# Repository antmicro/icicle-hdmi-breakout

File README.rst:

====================
Icicle HDMI breakout
====================

Copyright (c) 2020 `Antmicro <https://www.antmicro.com>`_

.. figure:: img/icicle-hdmi-breakout.png

Overview
========

This repository contains open hardware design files for Antmicro's expansion board compatible with the `PolarFire SoC FPGA Icicle Evaluation Kit from Microchip. <https://www.microsemi.com/existing-parts/parts/152514>`_.
The design files were created in KiCad.
The expansion board breaks out an HDMI interface on a regular HDMI connector.
The TMDS data going out of this connector are connected to the FPGA fabric in `MPFS250T-FCVG484EES <https://www.microsemi.com/document-portal/doc_download/1244583-polarfire-soc-advance-datasheet>`_ PolarFire SoC.
The expansion board should be connected to the ``J26`` expansion connector on the Icicle board.
For more information regarding the electrical connections please refer to the schematic sheets and compare them against the `offcial documentation <https://www.microsemi.com/product-directory/soc-fpgas/5498-polarfire-soc-fpga#resources>`_ of the PolarFire Icicle kit.

Repository structure
--------------------

The main repository directory contains KiCad PCB project files, LICENSE and README.
The remaining files are stored in the following directories:

* ``3d-model`` - contains a `mechanical model <3d-model/icicle-hdmi-breakout.stl>`_ of the board in the stl mesh format
* ``lib`` - contains the component libraries
* ``doc`` - contains selected files for device fabrication (schematic in PDF, BoM)
* ``img`` - contains graphics for this README

Dimensions and layout
=====================

The image below presents the HDMI expansion board's dimensions and layout.

.. figure:: img/icicle-hdmi-breakout-mechanical.png

License
=======

`MIT <LICENSE>`_

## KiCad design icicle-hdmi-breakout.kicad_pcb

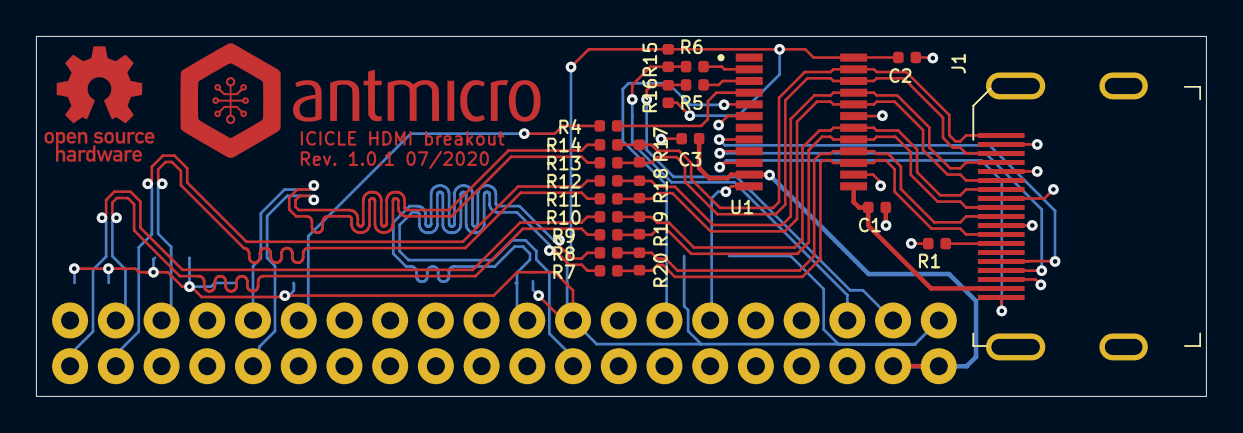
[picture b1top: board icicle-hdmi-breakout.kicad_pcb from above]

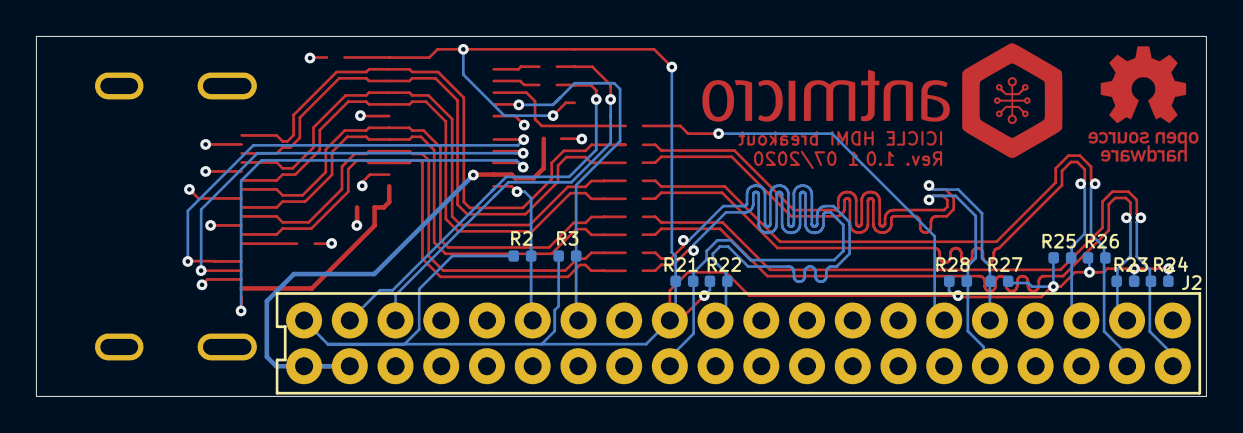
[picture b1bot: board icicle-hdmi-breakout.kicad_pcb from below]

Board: 4 copper layers, 65.0 x 20.0 mm, 36 parts (11 on the bottom side), 32 nets.

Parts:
C1, C2, C3: C_100n_0402_16V; 0402-cap
J1: 685119134923; HDMI_A_Female_685119134923
J2: 2x20_Header_Female; PinHeader_2x40_P2.54_Drill1mm
N1: antmicro_logo; antmicro-logo_scaled_20mm
N2: oshw_logo; oshw-logo
R1, R15, R16, R21, R22, R23, R24, R25, R26, R27, R28: R_10k_0402; 0402-res
R2, R3, R4, R5, R6, R7, R8, R9, R10, R11, R12, R13, R14: R_0R_0402; 0402-res
R17, R18, R19, R20: R_100R_0402; 0402-res
U1: TPD12S016PWR

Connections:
+3V3: C2.1, J2.1, J2.17, R2.1, R3.1, R15.1, R16.1, R21.1, R22.1, R23.1, R24.1, R25.1, R26.1, R27.1, R28.1, U1.24
+5V: C3.1, J2.2, J2.4, U1.11
/CLK_N: J2.18, R7.1, R21.2
/CLK_P: J2.19, R8.1, R22.2
/CT_HPD: J2.11, R2.2, U1.12
/DATA_0_N: J2.37, R9.1, R23.2
/DATA_0_P: J2.40, R10.1, R24.2
/DATA_1_N: J2.35, R11.1, R25.2
/DATA_1_P: J2.38, R12.1, R26.2
/DATA_2_N: J2.31, R13.1, R27.2
/DATA_2_P: J2.32, R14.1, R28.2
/EDID_SCL: J2.5, R6.1, R15.2
/EDID_SDA: J2.3, R5.1, R16.2
/HPD: J2.29, R4.1
/LS_OE: J2.13, R3.2, U1.5
/OUT_CLK_N: J1.12, R7.2, R20.1, U1.15
/OUT_CLK_P: J1.10, R8.2, R20.2, U1.16
/OUT_DATA_0_N: J1.9, R9.2, R19.1, U1.17
/OUT_DATA_0_P: J1.7, R10.2, R19.2, U1.18
/OUT_DATA_1_N: J1.6, R11.2, R18.1, U1.20
/OUT_DATA_1_P: J1.4, R12.2, R18.2, U1.21
/OUT_DATA_2_N: J1.3, R13.2, R17.1, U1.22
/OUT_DATA_2_P: J1.1, R14.2, R17.2, U1.23
/OUT_EDID_SCL: J1.15, U1.8
/OUT_EDID_SDA: J1.16, U1.9
/OUT_HPD: J1.19, U1.10
GND: C1.2, C2.2, C3.2, J1.2, J1.5, J1.8, J1.11, J1.17, J1.SH, J2.6, J2.9, J2.14, J2.20, J2.25, J2.30, J2.34, J2.39, R1.2, U1.6, U1.14, U1.19
HDMI_PWR: C1.1, J1.18, U1.13
unnamed: J1.13, R1.1
unnamed: R4.2, U1.4
unnamed: R5.2, U1.3
unnamed: R6.2, U1.2

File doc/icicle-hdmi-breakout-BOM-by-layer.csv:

Reference,Quantity,Value,Footprint,Manufacturer,MPN,Layer,
C1 C2 C3,3,C_100n_0402_16V,0402-cap,MULTICOMP,MC0402B104K160CT,Top,
J1,1,685119134923,HDMI_A_Female_685119134923,Amphenol,685119134923,Top,
R15 R16,2,R_10k_0402,0402-res,VISHAY,CRCW040210K0FKEDHP,Top,
R17 R18 R19 R20,4,R_100R_0402,0402-res,BOURNS,CR0402-FX-1000GLF,Top,
R4 R5 R6 R7 R8 R9 R10 R11 R12 R13 R14,11,R_0R_0402,0402-res,PANASONIC,ERJ2GE0R00X,Top,
U1,1,TPD12S016PWR,TPD12S016PWR,Texas Instruments,TPD8S009DSMR,Top,
J2,1,2x20_Header_Female,PinHeader_2x40_P2.54_Drill1mm,MULTICOMP,2214S-40SG-85 ,Bottom,
R2 R3,2,R_0R_0402,0402-res,PANASONIC,ERJ2GE0R00X,Bottom,
R1 R21 R22 R23 R24 R25 R26 R27 R28,9,R_10k_0402,0402-res,VISHAY,CRCW040210K0FKEDHP,DNP,
N1,1,antmicro_logo,antmicro-logo,,,Virtual,
N2,1,oshw_logo,oshw-logo,,,Virtual,

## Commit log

2020-07-22 Add release 1.0.1
2020-07-24 README updates
2020-07-24 Add mechanical drawings
2020-07-24 Add BOM
2021-04-27 Fix readme syntax
2021-06-24 Notes added by 'git notes add'
